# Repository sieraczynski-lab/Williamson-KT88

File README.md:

# Williamson KT88

Lampowy wzmacniacz push-pull w klasycznej topologii Williamsona (wszystkie lampy sterujące na 6SN7), z końcówką na parze KT88 w układzie ultralinearnym (UL). Projekt to wzmacniacz **onyx1944** na jego płytce VA1523:

- wersja na KT88 (zdjęcia, PCB): https://onyx1944.wordpress.com/2023/11/21/williamson-kt88/
- wersja na 6S33S (schemat i zasilacz): https://onyx1944.wordpress.com/2020/03/16/6s33s-williamson-amplifier/

Płytka **VA1523-V1.0** jest kupiona od Onyxa (bez lamp i transformatorów), a Onyx udostępnił schematy. Schemat w tym repozytorium jest przerysowany z jego schematu i **poprawiony według wartości faktycznie wlutowanych na płytce**. Pomarańczowe elementy to te, które trzeba sprawdzić albo dobrać pod toroid TTG-KT88PP i własny transformator sieciowy. Oryginalnych plików Onyxa tu nie ma, to jego praca.

> **Status: płytka w ręku, przed uruchomieniem.** Punkty pracy są szacunkowe (model lampy, Ua ≈ 465 V), do potwierdzenia pomiarem.

> ⚠️ **Wysokie napięcie.** Ua ok. 465 V, a na zimno i przy wysokim napięciu sieci więcej. Kondensatory filtrów rozładowują się przez rezystory 560 k i dzielnik żarzenia; to trwa od kilkudziesięciu sekund do kilku minut. Przed dotknięciem płytki zawsze zmierz napięcie.

## Schematy

| Plik | Zawartość |
|---|---|
| [`schematy/kanal.svg`](schematy/kanal.svg) | Jeden kanał wg VA1523: 6SN7 (wejście + katodyna) → 6SN7 (driver) → 2× KT88 UL, bias osobno dla każdej lampy |
| [`schematy/zasilacz.svg`](schematy/zasilacz.svg) | Zasilacz z płytki (osobno w każdym kanale): mostek, CLC z dławikiem 10 H, Uaa przez R128, bias, podniesienie żarzenia |
| [`schematy/plytka_zasilacza.svg`](schematy/plytka_zasilacza.svg) | Własna płytka zasilacza: bezpieczniki, miękki start K1/K2, opóźnione anody K3/K4 z R_IN, napięcia przemienne do płytki Onyxa, pomiar Ua i dioda HV |
| [`pcb/`](pcb/) | Płytki do zamówienia (KiCad 4 dla EasyEDA Standard, 5 dla EasyEDA Pro i KiCad 8, z klasami sieci): nowy zasilacz 100 × 100 mm, nowa płytka UL/trioda na oba kanały (4 przekaźniki, 100 × 66 mm) oraz z Soloista sterowanie ESP32, przełącznik kolumn, selektor. Połączenia: [`pcb/CZYTAJ_MNIE.txt`](pcb/CZYTAJ_MNIE.txt) |
| [`docs/soloist/`](docs/soloist/) | Opis sterowania i selektora (kopia z Soloista) |
| [`schematy/ul_trioda.svg`](schematy/ul_trioda.svg) | Okablowanie przełącznika UL / trioda: toroid, płytka UL, J101 Onyxa |
| [`schematy/williamson-kt88.html`](schematy/williamson-kt88.html) | Oba schematy z punktami pracy, różnicami płytka/schemat, listą zmian i uruchomieniem (otwórz w przeglądarce) |

## Najważniejsze dane

| | Wartość |
|---|---|
| Lampy | V1, V2: 6SN7 (6N8S); V5, V6: KT88 (lewy kanał; prawy V3, V4, V7, V8) |
| Front end | wejście ok. 4,3 mA / 95 V, katodyna 22k/22k ok. 4,5 mA, driver ok. 5 mA na triodę (bez balansu AC) |
| Końcówka | KT88 UL, Ua ≈ 465 V, 50–55 mA (0,50–0,55 V na 10 Ω), Ug1 ≈ −45…−55 V |
| Transformator wyjściowy | toroidy.pl **TTG-KT88PP** (u Onyxa Hammond 1650HA 6,6 kΩ) |
| Sprzężenie zwrotne | R129 15k z **odczepu 8 Ω** (ok. 12 dB), C123 niemontowany |
| Czułość / moc | ok. 0,65 V / ok. 40 W na kanał, kolumny na odczepie 4 Ω |
| Transformator sieciowy | 400 VA: 360 V (odczepy 345/375 V)/0,65 A, 58 V/100 mA, 6,3 V/8 A, 6,3 V/3 A, ekran ([docs/08](docs/08-zamowienie-toroidy.md)) |
| Dławiki | 2× 10 H / 250 mA / 45 Ω na L106 / L206 |

## Płytka a schemat Onyxa

| Element | Na schemacie | Na płytce |
|---|---|---|
| R117 / R217 | 220k / 1k | **100k / 100k** |
| R124 / R224 | 10 Ω / 470k | **10 Ω / 10 Ω** |
| C123 / C223 | 56 pF | **brak** |
| R101 | 1M | **220k** |
| R103 | 47k | **33k** |
| R104 / C102 | 47 Ω / 47 µF | **zwora / brak** |
| R111, R112 | 470k | **300k** |
| R119, R120 | 470k | **68k** |
| P101, P102 | 47k | **20k** |
| R139, R140 | 47k | **4k7** |
| R129 | 22k | **15k** |
| R134 | 10 Ω | **5,1 Ω** |
| R136 / R137 | 100k / 10k | **brak** w lewym, **300k / 68k** w prawym |
| R130–R133 | 330 Ω | **390 Ω** |
| R143–R152 | 680k | **560k** |
| R125, R126 | 100 Ω | **150 Ω** |
| R141, R142 | 10 Ω / 100 Ω | **47 Ω / 47 Ω** |

## Zasilacz, sterowanie, dodatki i obudowa

Płytka Onyxa dostaje własną, prostą płytkę zasilacza (bez prostowników i filtrów, bo te są na płytce Onyxa): miękki start, opóźnione anody, pomiar Ua. Z [Soloist-KT88](https://github.com/sieraczynski-lab/Soloist-KT88) bierze sterownik ESP32 z automatyczną korektą biasu, układ przełącznika UL / trioda (tu jedna płytka na oba kanały), przełącznik kolumn z triggerem, selektor z drabinką głośności i obudowę. Te płytki Soloista bez zmian w PCB, płytka Onyxa bez cięcia ścieżek. Szczegóły: [docs/09-integracja-soloist.md](docs/09-integracja-soloist.md), obudowa: [`obudowa/`](obudowa/).

## Decyzje i otwarte sprawy

- **Toroid TTG-KT88PP** zamiast Hammonda: sprzężenie zwrotne z odczepu 8 Ω (zbliżona głębokość pętli jak u Onyxa), kolumny na 4 Ω. Kompensację C123 dobrać na oscyloskopie, jeśli prostokąt dzwoni.
- **R128 / R228** (4k7) dobrać do własnego Ua, żeby Uaa wyszło ok. 380–420 V.
- **Driver bez balansu AC:** do V2 dawać 6SN7 o zbliżonych prądach obu triod.
- **Dodatek:** rezystor 100 Ω / 2 W między 4 Ω a COM (wzmacniacz nie pracuje bez obciążenia).
- **Odpowiedzi Onyxa (12.11.2026):** u niego TR1 to toroidy.pl TSTA-0300/001 (300 VA), radzi większy, więc 400 VA jest w porządku. Sprzężenie zwrotne z odczepu 8 Ω (zgodnie z planem). C123 i ewentualnie R102/C101 tylko pod prostokąt (u niego niepotrzebne). Pomyłki na schemacie potwierdzone. Szczegóły w [docs/07](docs/07-wersje-onyxa.md#odpowiedzi-onyxa-12112026).
- **Sprawdzone:** sieć UaFF-L2 (środek żarzenia KT88) to masa (wspólny punkt C108, C126, R142).
- Projekt równoległy: [Soloist-KT88](https://github.com/sieraczynski-lab/Soloist-KT88) (Mullard: EF86 + E88CC LTP + KT88), z podobnym transformatorem sieciowym i tymi samymi toroidami.

## Notatki

1. [Lampy KT88 Psvane: serie i różnice](docs/01-lampy-kt88.md)
2. [Transformatory wyjściowe: Hammond, toroidy.pl, Ogonowski](docs/02-transformatory-wyjsciowe.md)
3. [Topologia: Williamson, Mullard 5-20, 6S33S, 6SN7](docs/03-topologia.md)
4. [Kolumny: impedancja, zwrotnica 2,5-drożna, spadek bafla](docs/04-kolumny.md)
5. [Uruchomienie krok po kroku](docs/05-uruchomienie.md)
6. [Zamawianie płytek PCB](docs/06-pcb.md)
7. [Wersje Onyxa: zdjęcia, schemat i płytka VA1523](docs/07-wersje-onyxa.md)
8. [Specyfikacja do zamówienia w toroidy.pl](docs/08-zamowienie-toroidy.md)
9. [Zasilacz, sterowanie, dodatki i obudowa](docs/09-integracja-soloist.md)

## Generowanie schematów

Schematy są rysowane skryptem (Python 3, bez dodatkowych bibliotek):

```bash
python3 narzedzia/build.py
```

Obudowa (STEP, DXF, widoki) powstaje z `python3 narzedzia/obudowa/export.py` (wymaga `numpy` i `matplotlib`).

Skrypt [`narzedzia/gen_schemat.py`](narzedzia/gen_schemat.py) zawiera geometrię i wartości elementów. Po zmianie wartości wystarczy uruchomić `build.py` ponownie, a SVG i strona HTML w `schematy/` zostaną odświeżone.

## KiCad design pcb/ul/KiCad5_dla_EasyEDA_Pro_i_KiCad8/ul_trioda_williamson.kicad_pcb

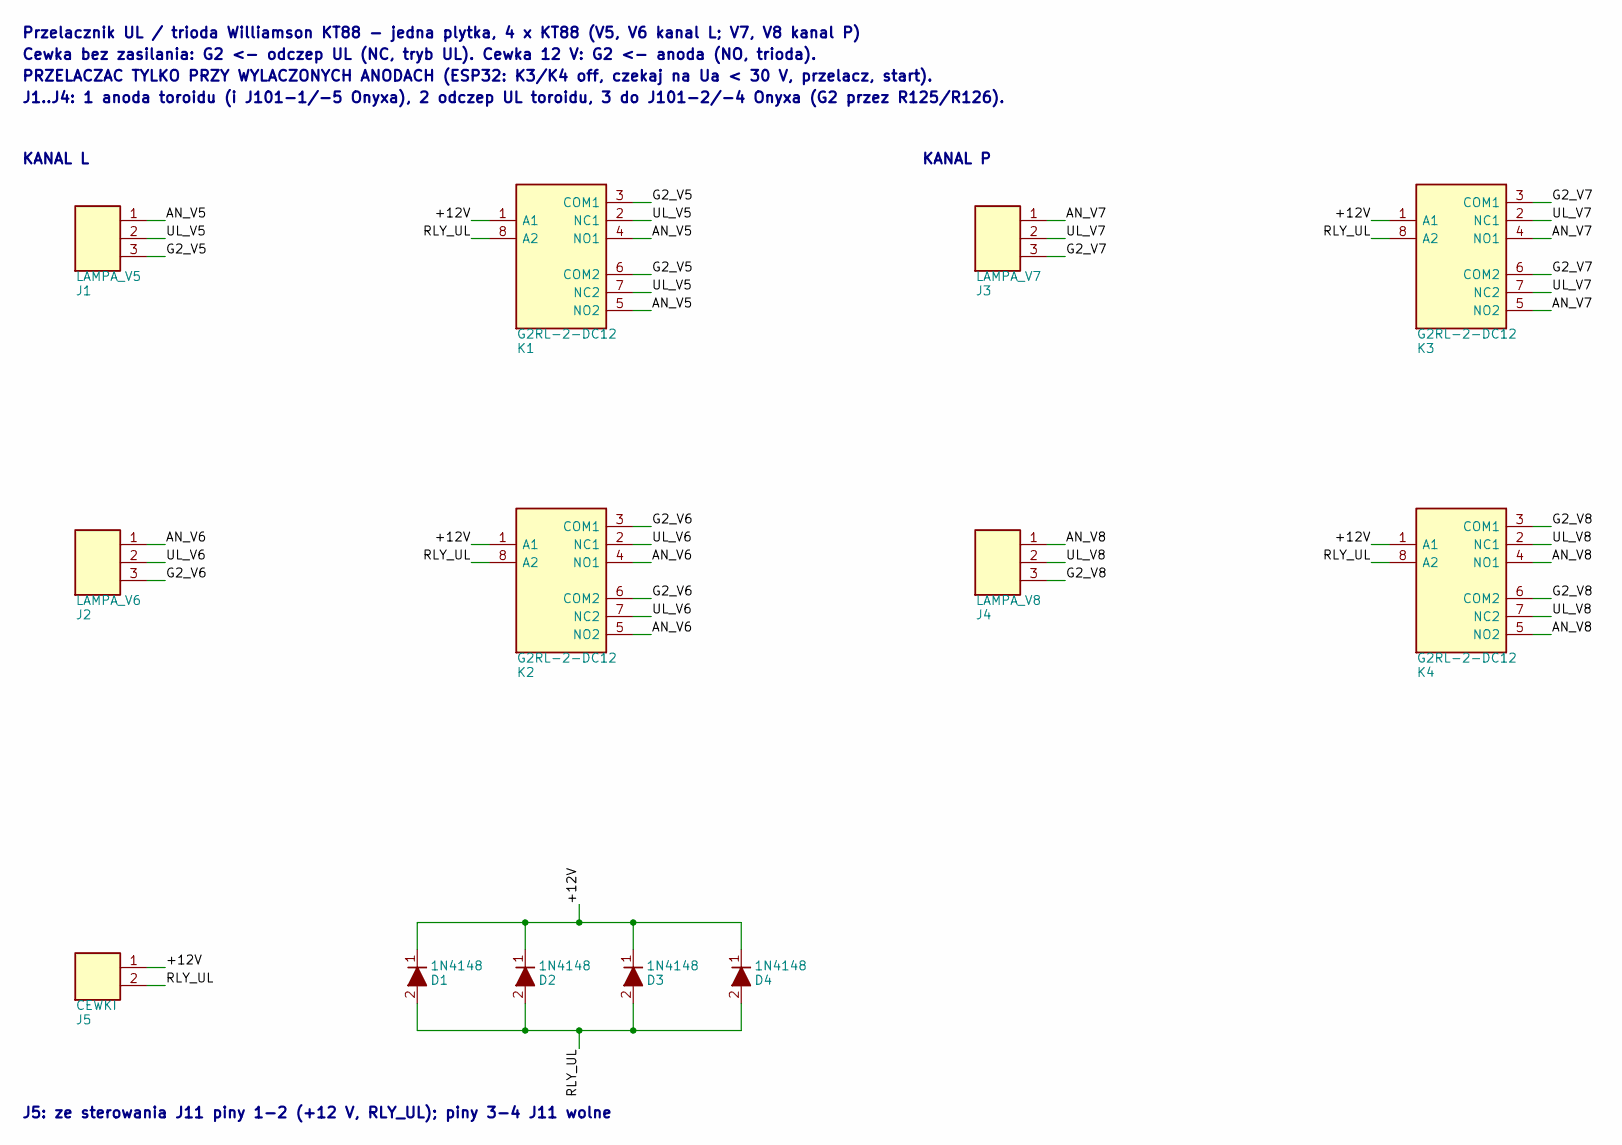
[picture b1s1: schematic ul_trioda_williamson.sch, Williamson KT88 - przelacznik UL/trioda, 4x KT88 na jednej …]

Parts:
D1, D2, D3, D4: 1N4148; D_DO-35_P7.62
J1: LAMPA_V5; TerminalBlock_1x03_P7.62_V
J2: LAMPA_V6; TerminalBlock_1x03_P7.62_V
J3: LAMPA_V7; TerminalBlock_1x03_P7.62_V
J4: LAMPA_V8; TerminalBlock_1x03_P7.62_V
J5: CEWKI; TerminalBlock_1x02_P5.08
K1, K2, K3, K4: G2RL-2-DC12; Relay_DPDT_Omron_G2RL

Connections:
+12V: D1.1 (K), D2.1 (K), D3.1 (K), D4.1 (K), J5.1, K1.1 (A1), K2.1 (A1), K3.1 (A1), K4.1 (A1)
AN_V5: J1.1, K1.4 (NO1), K1.5 (NO2)
AN_V6: J2.1, K2.4 (NO1), K2.5 (NO2)
AN_V7: J3.1, K3.4 (NO1), K3.5 (NO2)
AN_V8: J4.1, K4.4 (NO1), K4.5 (NO2)
G2_V5: J1.3, K1.3 (COM1), K1.6 (COM2)
G2_V6: J2.3, K2.3 (COM1), K2.6 (COM2)
G2_V7: J3.3, K3.3 (COM1), K3.6 (COM2)
G2_V8: J4.3, K4.3 (COM1), K4.6 (COM2)
RLY_UL: D1.2 (A), D2.2 (A), D3.2 (A), D4.2 (A), J5.2, K1.8 (A2), K2.8 (A2), K3.8 (A2), K4.8 (A2)
UL_V5: J1.2, K1.2 (NC1), K1.7 (NC2)
UL_V6: J2.2, K2.2 (NC1), K2.7 (NC2)
UL_V7: J3.2, K3.2 (NC1), K3.7 (NC2)
UL_V8: J4.2, K4.2 (NC1), K4.7 (NC2)

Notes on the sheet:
Przelacznik UL / trioda Williamson KT88 - jedna plytka, 4 x KT88 (V5, V6 kanal L; V7, V8 kanal P)
Cewka bez zasilania: G2 <- odczep UL (NC, tryb UL). Cewka 12 V: G2 <- anoda (NO, trioda).
PRZELACZAC TYLKO PRZY WYLACZONYCH ANODACH (ESP32: K3/K4 off, czekaj na Ua < 30 V, przelacz, start).
J1..J4: 1 anoda toroidu (i J101-1/-5 Onyxa), 2 odczep UL toroidu, 3 do J101-2/-4 Onyxa (G2 przez R125/R126).
KANAL L
KANAL P
J5: ze sterowania J11 piny 1-2 (+12 V, RLY_UL); piny 3-4 J11 wolne

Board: 2 copper layers, 17 parts (0 on the bottom side), 14 nets, no tracks yet.

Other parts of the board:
MH1, MH2, MH3, MH4: M3; MountingHole_M3

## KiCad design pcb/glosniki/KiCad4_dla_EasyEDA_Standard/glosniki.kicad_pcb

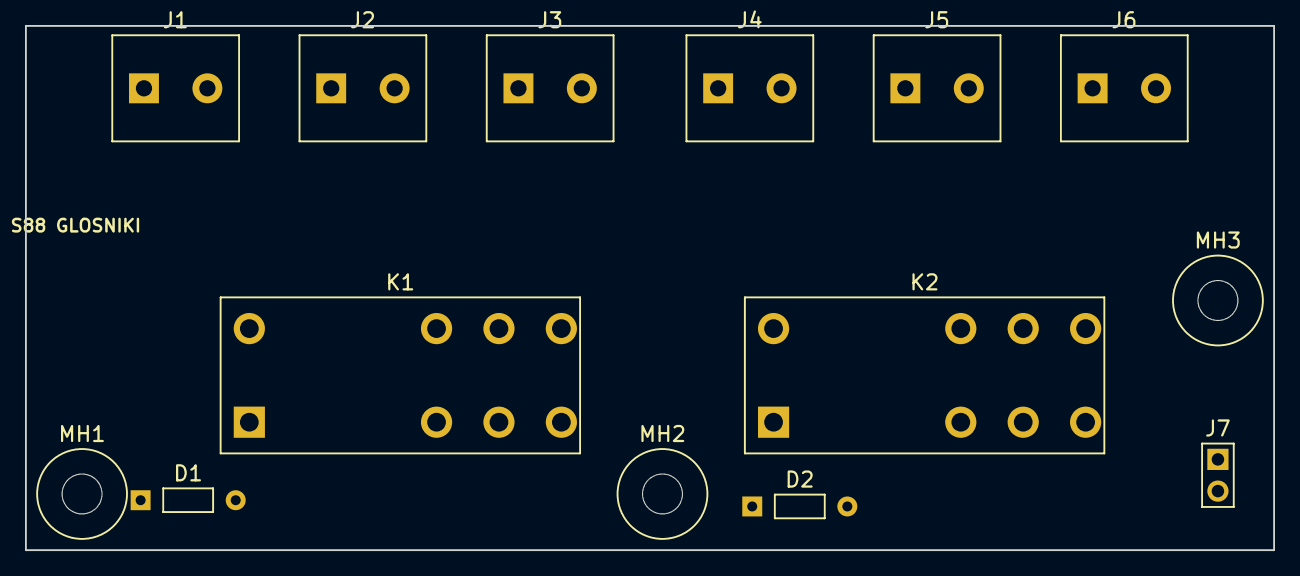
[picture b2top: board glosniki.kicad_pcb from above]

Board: 2 copper layers, 100.0 x 42.0 mm, 14 parts (0 on the bottom side), 14 nets, no tracks yet.

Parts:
D1, D2: 1N4148; D_DO-35_P7.62
J1: MARANTZ_L; TerminalBlock_1x02_P5.08
J2: LAMPA_L; TerminalBlock_1x02_P5.08
J3: KOLUMNA_L; TerminalBlock_1x02_P5.08
J4: MARANTZ_R; TerminalBlock_1x02_P5.08
J5: LAMPA_R; TerminalBlock_1x02_P5.08
J6: KOLUMNA_R; TerminalBlock_1x02_P5.08
J7: CEWKI; PinHeader_1x02_P2.54
K1, K2: G2RL-2-DC12; Relay_DPDT_Omron_G2RL
MH1, MH2, MH3: M3; MountingHole_M3

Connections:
+12V: D1.1, D2.1, J7.1, K1.1, K2.1
MAR_LN: J1.2, K1.7
MAR_LP: J1.1, K1.2
MAR_RN: J4.2, K2.7
MAR_RP: J4.1, K2.2
RLY_SPK: D1.2, D2.2, J7.2, K1.8, K2.8
SPK_LN: J3.2, K1.6
SPK_LP: J3.1, K1.3
SPK_RN: J6.2, K2.6
SPK_RP: J6.1, K2.3
TUBE_LN: J2.2, K1.5
TUBE_LP: J2.1, K1.4
TUBE_RN: J5.2, K2.5
TUBE_RP: J5.1, K2.4

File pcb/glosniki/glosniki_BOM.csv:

Oznaczenie;Wartosc;Footprint;Strona;X [mm];Y [mm];Grupa;LCSC;Uwagi
K1;G2RL-2-DC12;Relay_DPDT_Omron_G2RL;GORA;30.00;28.00;PRZEKAZNIKI GLOSNIKOW;C61458;"kanal L: bez pradu cewki kolumna <- Marantz (NC), cewka zasilona: kolumna <- Lampa (NO); + i - przelaczane"
K2;G2RL-2-DC12;Relay_DPDT_Omron_G2RL;GORA;72.00;28.00;PRZEKAZNIKI GLOSNIKOW;C61458;"kanal R: bez pradu cewki kolumna <- Marantz (NC), cewka zasilona: kolumna <- Lampa (NO); + i - przelaczane"
D1;1N4148;D_DO-35_P7.62;GORA;13.00;38.00;PRZEKAZNIKI GLOSNIKOW;;dioda cewki K1
D2;1N4148;D_DO-35_P7.62;GORA;62.00;38.50;PRZEKAZNIKI GLOSNIKOW;;dioda cewki K2
J1;MARANTZ_L;TerminalBlock_1x02_P5.08;GORA;12.00;5.00;ZLACZA;;z wyjscia glosnikowego Marantza, kanal L: 1 +, 2 -
J2;LAMPA_L;TerminalBlock_1x02_P5.08;GORA;27.00;5.00;ZLACZA;;z wtornego T101: 1 odczep 4 Ohm, 2 COM (masa Lampy)
J3;KOLUMNA_L;TerminalBlock_1x02_P5.08;GORA;42.00;5.00;ZLACZA;;do zaciskow kolumny L na tylnej sciance: 1 +, 2 -
J4;MARANTZ_R;TerminalBlock_1x02_P5.08;GORA;58.00;5.00;ZLACZA;;z Marantza, kanal R
J5;LAMPA_R;TerminalBlock_1x02_P5.08;GORA;73.00;5.00;ZLACZA;;z wtornego T201: 1 odczep 4 Ohm, 2 COM
J6;KOLUMNA_R;TerminalBlock_1x02_P5.08;GORA;88.00;5.00;ZLACZA;;do zaciskow kolumny R
J7;CEWKI;PinHeader_1x02_P2.54;GORA;95.50;36.00;ZLACZA;;z plytki sterowania J13
MH1;M3;MountingHole_M3;GORA;4.50;37.50;OTWORY;;
MH2;M3;MountingHole_M3;GORA;51.00;37.50;OTWORY;;
MH3;M3;MountingHole_M3;GORA;95.50;22.00;OTWORY;;

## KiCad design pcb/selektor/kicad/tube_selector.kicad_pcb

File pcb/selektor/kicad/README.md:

# TubeSel v0.5: selektor 4 wejść + drabinka przekaźnikowa 63 dB + sterownik I²C

Projekt KiCad 8 (otwiera się też w KiCad 9 i nowszych).

## Zawartość
- `tube_selector.kicad_pro`: projekt (klasy sieci Audio 0,4 mm / Coil 0,3 mm)
- `tube_selector.kicad_sch`: schemat (A3)
- `tube_selector.kicad_pcb`: płytka 96 × 74 mm, 2 warstwy, elementy rozmieszczone, strefy mas na obu warstwach, **bez ścieżek**
- `TubeSel.kicad_sym` + `sym-lib-table`: biblioteka symboli projektu
- `TubeSel.pretty` + `fp-lib-table`: footprint modułu DC-DC
- `BOM.csv`: lista elementów z numerami LCSC (separator `;`)
- `JLCPCB_BOM.csv`: BOM w formacie JLCPCB do zamówienia montażu (tylko elementy SMD)
- `LCSC_zamowienie.csv`: komplet elementów do samodzielnego montażu (2 płytki + zapas, ze złączami JST) do wgrania w narzędziu BOM na lcsc.com
- Podgląd schematu i rozmieszczenia: [`docs/img/selektor_*.png`](../../../docs/img/)
- Pełna dokumentacja: [`docs/11-selektor.md`](../../../docs/11-selektor.md)
- Pliki projektu wygenerował skrypt `src/selektor/gen.py`. **Po rozpoczęciu trasowania w KiCadzie źródłem prawdy są pliki KiCad.** Ponowne uruchomienie generatora (`src/selektor/gen.py`) nadpisze ścieżki (zobacz [`src/selektor/README.md`](../../../src/selektor/README.md)).

## Układ
- **Selektor K1–K4:** COM = wejście, NO = wspólna szyna, NC = 1 kΩ do masy.
- **Drabinka K5–K10:** bity 1/2/4/8/16/32 dB, impedancja ok. 10 kΩ (9,6–10,8 kΩ), rezystory cienkowarstwowe 0,1% w wartościach dostępnych w JLCPCB/LCSC. Cewka ON = stopień tłumi. Błąd tłumienia ≤ 0,21 dB dla wszystkich 64 kodów (symulacja); kanały L i R mają identyczne wartości.

| Bit | Rs | Rp |
|---|---|---|
| −1 dB | 1,10k | 80,6k |
| −2 dB | 2,00k | 32,4k |
| −4 dB | 3,75k | 17,4k |
| −8 dB | 6,20k | 6,81k |
| −16 dB | 9,10k | 2,00k |
| −32 dB | 10,0k | 270R |
- **R33/R34 10 kΩ:** terminator, wymagany do poprawnych tłumień.
- **K11 mute (fail-safe):** bez prądu cewki wyjście jest zwarte do masy. Dźwięk dopiero po załączeniu K11.
- **Sterownik:** U1 MCP23017 (I²C) → U2, U3 ULN2803 (UTC ULN2803G-S18-R, LCSC C33924; dowolny ULN2803 w SOIC-18 300 mil pasuje) → cewki. Diody gaszące są w ULN2803 (COM → +12 V).

| Wyjście MCP23017 | Przekaźnik | Funkcja |
|---|---|---|
| GPA0–GPA3 | K1–K4 | wejście 1–4 |
| GPA4–GPA7 | K5–K8 | −1, −2, −4, −8 dB |
| GPB0–GPB1 | K9–K10 | −16, −32 dB |
| GPB2 | K11 | mute (H = dźwięk) |
| GPB3–GPB7 | — | wolne |

Wyjście w stanie H = cewka załączona.

- **Zasilanie:** płytka potrzebuje tylko +12 V. 3,3 V dla MCP23017 i pull-upów I²C daje moduł DC-DC U4 (wersja 3,3 V; pinout 1 −IN, 2 +IN, 3 OUT+, 4 OUT−; rozstaw 14,17 × 8,24 mm). Pobór z 3,3 V to kilka mA.
- **J6 (JST XH 6p) do ESP32:** 1 +12 V, 2 DGND, 3 n/c, 4 SDA, 5 SCL, 6 DGND. Pin 3 celowo nie jest podłączony: nie łącz 3,3 V z ESP32 z 3,3 V tej płytki (dwa źródła napięcia).
- **Adres I²C:** SJ1–SJ3 otwarte = **0x20**. Zwarcie SJn ustawia bit An (0x20–0x27). Jeśli na tej samej magistrali jest drugi MCP23017 (np. od przekaźników biasu), ustaw tu inny adres.
- **Pull-upy I²C 4,7 kΩ (R36, R37)** są na płytce. Jeśli ESP32 też ma swoje, nic się nie stanie.

## Masy
- **GND (audio)** i **DGND (cyfrowa)** to osobne sieci i osobne strefy miedzi. DGND zajmuje dolny pas płytki pod układami scalonymi.
- **R41 (0 Ω, domyślnie nie montować)** łączy je w jednym punkcie. Zostaw puste, jeśli masa ESP32 łączy się z masą wzmacniacza w gwieździe gdzie indziej (tak jest najlepiej). Zmontuj tylko wtedy, gdy DGND nie ma innego połączenia z masą wzmacniacza.
- **R35 (0 Ω, DNP)** łączy masę audio z obudową przez MH1.

## Do sprawdzenia przed zamówieniem
1. **Biegunowość cewki G6K-2F-Y: potwierdzona.** Pin 1 = +12 V, pin 8 = do ULN2803. Przy lutowaniu ustaw znacznik pinu 1 na obudowie przekaźnika zgodnie ze znacznikiem na sitodruku; odwrotnie wlutowany polaryzowany przekaźnik nie zadziała.
2. Kolejność pinów kabli audio na J1–J5 (sitodruk „R G L”).
3. **Footprint modułu DC-DC** odwzorowałem ze zrzutu ekranu: otwory 1,0 mm, pady 2,2 mm, obrys 17,6 × 12,2 mm. Zmierz suwmiarką swój moduł (średnicę pinów i obrys) albo podmień footprint na własny.
4. Moduł DC-DC przy obciążeniu kilku mA zwykle pracuje w trybie impulsowym (burst). Jeśli w głośnikach pojawi się cichy szum lub „ćwierkanie”, pomoże dławik/ferryt w linii +3V3 albo zastąpienie modułu stabilizatorem 78L33.

## Kroki w KiCadzie
1. Otwórz `tube_selector.kicad_pro`.
2. Schemat: Inspect → Electrical Rules Checker.
3. PCB: Tools → Update PCB from Schematic (powinno nie wykryć zmian), poprowadź ścieżki (ręcznie lub wtyczką Freerouting), naciśnij **B** (wypełnienie stref) i uruchom DRC.

## Wskazówki do trasowania
- Tor audio na warstwie TOP, krótko; BOTTOM w części audio w miarę możliwości jako ciągła masa.
- Linie cewek (ULN → przekaźniki) i +12 V prowadź z dala od wejść, najlepiej prostopadle do ścieżek audio.
- Żadna ścieżka cyfrowa (SDA, SCL, DRV) nie powinna wchodzić w część audio.
- Kanały L (pady po prawej stronie przekaźników) i R (po lewej) rozdzielaj masą.

## Sterowanie
Zmiana głośności: najpierw ZAŁĄCZ nowe bity, odczekaj ~5 ms, potem WYŁĄCZ zbędne. Przejście zawsze idzie przez stan cichszy.
Po starcie MCP23017 ma wszystkie piny jako wejścia, więc wszystkie przekaźniki są wyłączone: wejście 1 niewybrane, tłumienie 0 dB i **mute aktywny**. Odblokowanie dźwięku następuje dopiero, gdy firmware ustawi wejście, głośność i GPB2 = 1.

## Montaż w JLCPCB
- `JLCPCB_BOM.csv` zawiera wszystkie elementy SMD z numerami LCSC (stan magazynu sprawdzony 22.10.2026). Plik pozycji (CPL) wygeneruj w KiCadzie po poprowadzeniu ścieżek: File → Fabrication Outputs → Component Placement (.pos), format CSV, jednostki mm.
- Złącza JST (J1–J6) i moduł DC-DC (U4) są przewlekane, więc najprościej przylutować je samemu.
- R35 i R41 (0 Ω, opcjonalne) są poza BOM-em JLCPCB.
- **Przed zatwierdzeniem zamówienia sprawdź w podglądzie JLCPCB orientację każdego przekaźnika i układu scalonego** (znacznik pinu 1). Obrócony G6K nie zadziała.

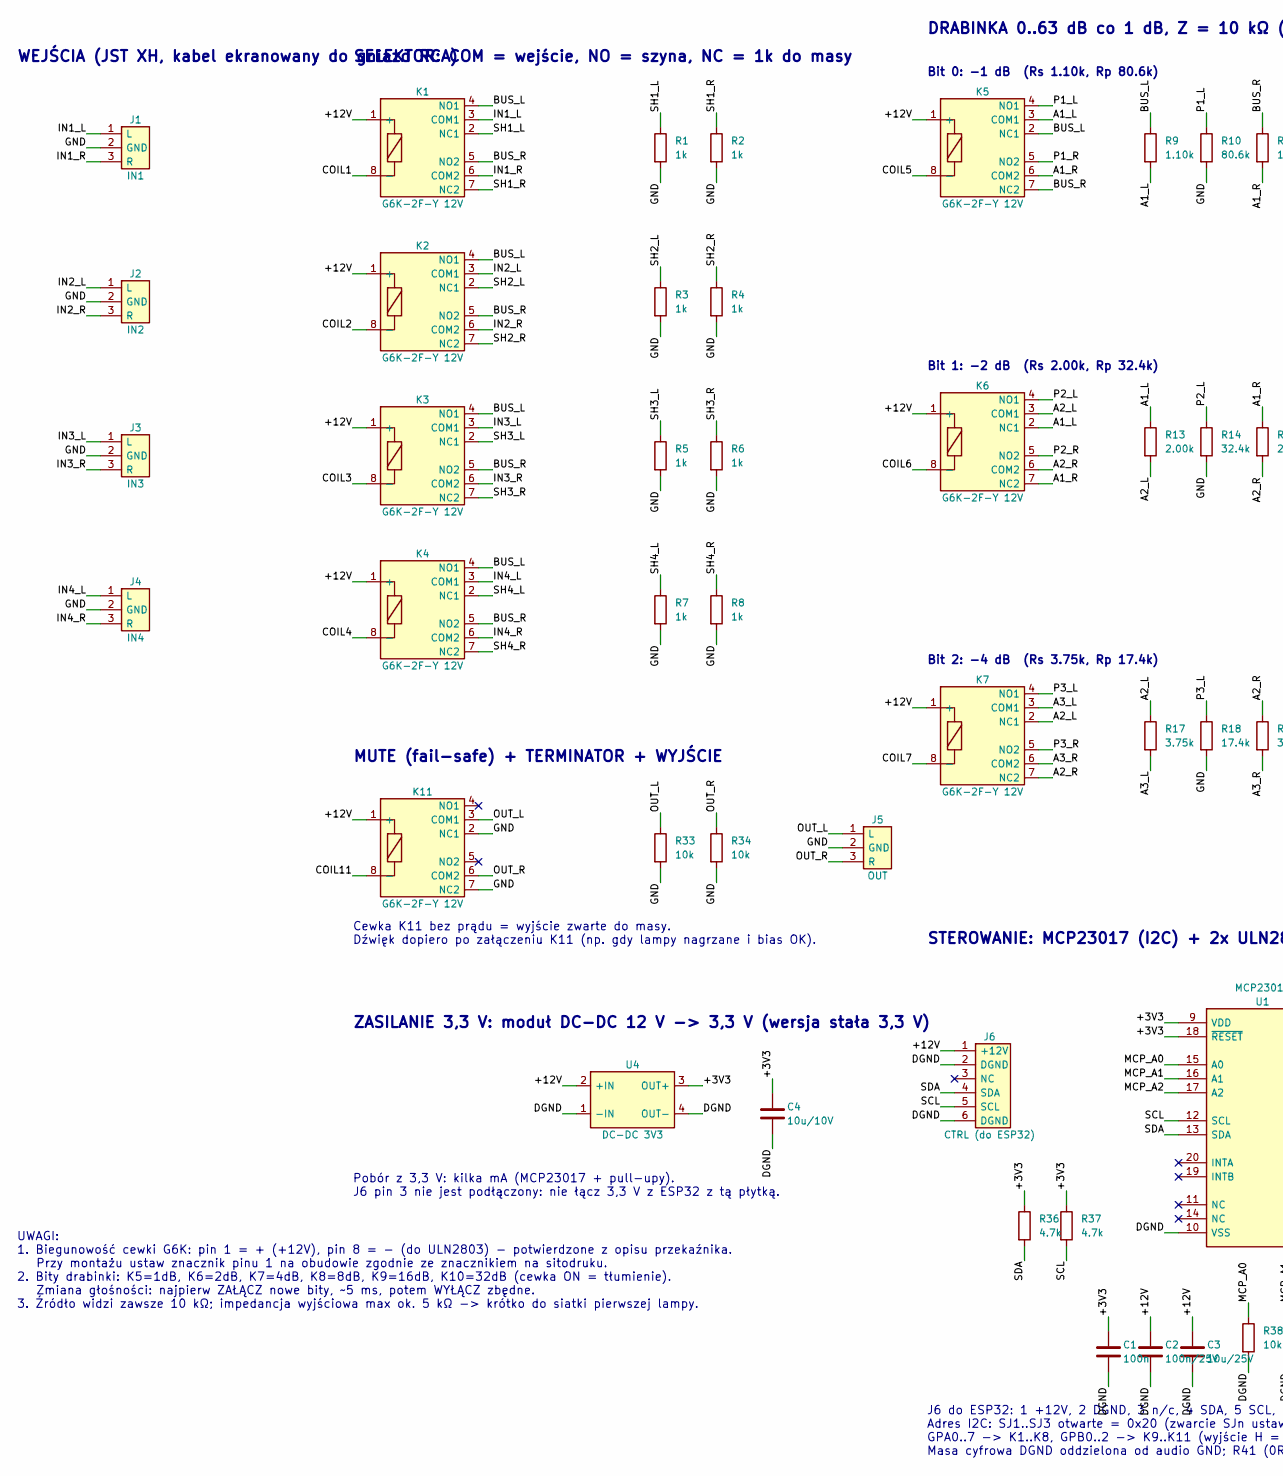
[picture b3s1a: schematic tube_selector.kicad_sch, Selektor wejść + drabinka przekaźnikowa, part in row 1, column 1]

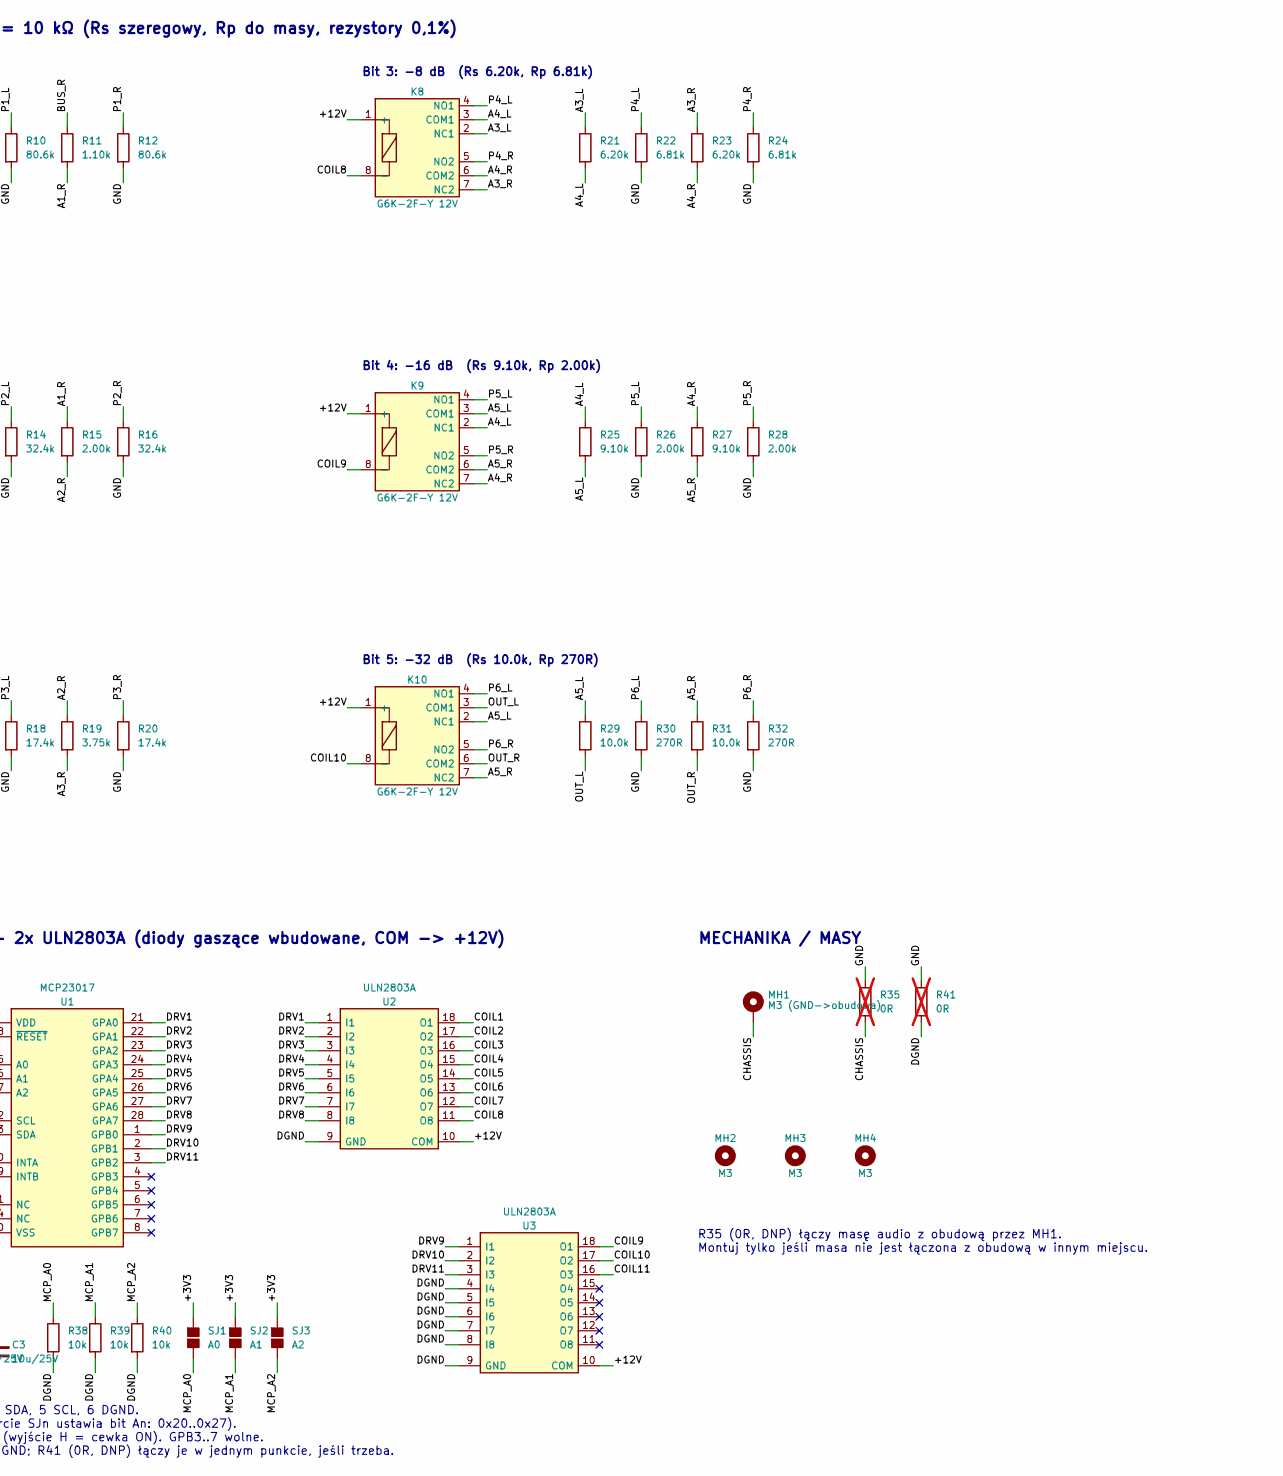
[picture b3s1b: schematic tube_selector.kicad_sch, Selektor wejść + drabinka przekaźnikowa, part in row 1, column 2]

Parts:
C1: 100n; C_0805_2012Metric; MPN CC0805KRX7R9BB104; LCSC C49678
C2: 100n/25V; C_0805_2012Metric; MPN CC0805KRX7R9BB104; LCSC C49678
C3: 10u/25V; C_1206_3216Metric; MPN CL31A106KBHNNNE; LCSC C13585
C4: 10u/10V; C_1206_3216Metric; MPN CL31A106KBHNNNE; LCSC C13585
J1: IN1; JST_XH_B3B-XH-A_1x03_P2.50mm_Vertical
J2: IN2; JST_XH_B3B-XH-A_1x03_P2.50mm_Vertical
J3: IN3; JST_XH_B3B-XH-A_1x03_P2.50mm_Vertical
J4: IN4; JST_XH_B3B-XH-A_1x03_P2.50mm_Vertical
J5: OUT; JST_XH_B3B-XH-A_1x03_P2.50mm_Vertical
J6: CTRL (do ESP32); JST_XH_B6B-XH-A_1x06_P2.50mm_Vertical; MPN JST B6B-XH-A + wtyk XHP-6
K1, K2, K3, K4, K5, K6, K7, K8, K9, K10, K11: G6K-2F-Y 12V; Relay_DPDT_Omron_G6K-2F-Y; MPN G6K-2F-Y-TR DC12; LCSC C397192
MH1: M3 (GND->obudowa); MountingHole_3.2mm_M3_Pad
MH2, MH3, MH4: M3; MountingHole_3.2mm_M3
R1, R2, R3, R4, R5, R6, R7, R8: 1k; R_0805_2012Metric; Tolerancja 1%; MPN 0805W8F1001T5E; LCSC C17513
R9, R11: 1.10k; R_0805_2012Metric; Tolerancja 0.1%; MPN ERA6AEB112V; LCSC C473284
R10, R12: 80.6k; R_0805_2012Metric; Tolerancja 0.1%; MPN RT0805BRD0780K6L; LCSC C728657
R13, R15, R26, R28: 2.00k; R_0805_2012Metric; Tolerancja 0.1%; MPN PTFR0805B2K00P9; LCSC C479096
R14, R16: 32.4k; R_0805_2012Metric; Tolerancja 0.1%; MPN TR0805B32K4P0550Z; LCSC C149970
R17, R19: 3.75k; R_0805_2012Metric; Tolerancja 0.1%; MPN AR05BTB3751A010; LCSC C374641
R18, R20: 17.4k; R_0805_2012Metric; Tolerancja 0.1%; MPN PTFR0805B17K4P9; LCSC C47115938
R21, R23: 6.20k; R_0805_2012Metric; Tolerancja 0.1%; MPN RT0805BRD076K2L; LCSC C326695
R22, R24: 6.81k; R_0805_2012Metric; Tolerancja 0.1%; MPN RT0805BRD076K81L; LCSC C728655
R25, R27: 9.10k; R_0805_2012Metric; Tolerancja 0.1%; MPN TC0525B9101T5G; LCSC C21571502
R29, R31: 10.0k; R_0805_2012Metric; Tolerancja 0.1%; MPN RT0805BRD0710KL; LCSC C110775
R30, R32: 270R; R_0805_2012Metric; Tolerancja 0.1%; MPN PTFR0805B270RN9; LCSC C351587
R33, R34: 10k; R_0805_2012Metric; Tolerancja 0.1%; MPN RT0805BRD0710KL; LCSC C110775
R35, R41: 0R; R_0805_2012Metric; not fitted
R36, R37: 4.7k; R_0805_2012Metric; Tolerancja 1%; MPN 0805W8F4701T5E; LCSC C17673
R38, R39, R40: 10k; R_0805_2012Metric; Tolerancja 1%; MPN 0805W8F1002T5E; LCSC C17414
SJ1: A0; SolderJumper-2_P1.3mm_Open_Pad1.0x1.5mm
SJ2: A1; SolderJumper-2_P1.3mm_Open_Pad1.0x1.5mm
SJ3: A2; SolderJumper-2_P1.3mm_Open_Pad1.0x1.5mm
U1: MCP23017; SOIC-28W_7.5x17.9mm_P1.27mm; MPN MCP23017-E/SO; LCSC C47023
U2, U3: ULN2803A; SOIC-18W_7.5x11.6mm_P1.27mm; MPN ULN2803G-S18-R (UTC); LCSC C33924
U4: DC-DC 3V3; DCDC_Mini_4pin_14.17x8.24mm; MPN Mini DC-DC step-down 3,3 V (pinout: 1 -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

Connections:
/+3V3: C1.1, C4.1, R36.1, R37.1, SJ1.1, SJ2.1, SJ3.1, U1.9 (VDD), U1.18 (~RESET), U4.3 (OUT+)
/+12V: C2.1, C3.1, J6.1 (+12V), K1.1 (+), K2.1 (+), K3.1 (+), K4.1 (+), K5.1 (+), K6.1 (+), K7.1 (+), K8.1 (+), K9.1 (+), K10.1 (+), K11.1 (+), U2.10 (COM), U3.10 (COM), U4.2 (+IN)
/A1_L: K5.3 (COM1), K6.2 (NC1), R9.2, R13.1
/A1_R: K5.6 (COM2), K6.7 (NC2), R11.2, R15.1
/A2_L: K6.3 (COM1), K7.2 (NC1), R13.2, R17.1
/A2_R: K6.6 (COM2), K7.7 (NC2), R15.2, R19.1
/A3_L: K7.3 (COM1), K8.2 (NC1), R17.2, R21.1
/A3_R: K7.6 (COM2), K8.7 (NC2), R19.2, R23.1
/A4_L: K8.3 (COM1), K9.2 (NC1), R21.2, R25.1
/A4_R: K8.6 (COM2), K9.7 (NC2), R23.2, R27.1
/A5_L: K9.3 (COM1), K10.2 (NC1), R25.2, R29.1
/A5_R: K9.6 (COM2), K10.7 (NC2), R27.2, R31.1
/BUS_L: K1.4 (NO1), K2.4 (NO1), K3.4 (NO1), K4.4 (NO1), K5.2 (NC1), R9.1
/BUS_R: K1.5 (NO2), K2.5 (NO2), K3.5 (NO2), K4.5 (NO2), K5.7 (NC2), R11.1
/CHASSIS: MH1.1, R35.2
/COIL1: K1.8 (-), U2.18 (O1)
/COIL2: K2.8 (-), U2.17 (O2)
/COIL3: K3.8 (-), U2.16 (O3)
/COIL4: K4.8 (-), U2.15 (O4)
/COIL5: K5.8 (-), U2.14 (O5)
/COIL6: K6.8 (-), U2.13 (O6)
/COIL7: K7.8 (-), U2.12 (O7)
/COIL8: K8.8 (-), U2.11 (O8)
/COIL9: K9.8 (-), U3.18 (O1)
/COIL10: K10.8 (-), U3.17 (O2)
/COIL11: K11.8 (-), U3.16 (O3)
/DGND: C1.2, C2.2, C3.2, C4.2, J6.2 (DGND), J6.6 (DGND), R38.2, R39.2, R40.2, R41.2, U1.10 (VSS), U2.9 (GND), U3.4 (I4), U3.5 (I5), U3.6 (I6), U3.7 (I7), U3.8 (I8), U3.9 (GND), U4.1 (-IN), U4.4 (OUT-)
/DRV1: U1.21 (GPA0), U2.1 (I1)
/DRV2: U1.22 (GPA1), U2.2 (I2)
/DRV3: U1.23 (GPA2), U2.3 (I3)
/DRV4: U1.24 (GPA3), U2.4 (I4)
/DRV5: U1.25 (GPA4), U2.5 (I5)
/DRV6: U1.26 (GPA5), U2.6 (I6)
/DRV7: U1.27 (GPA6), U2.7 (I7)
/DRV8: U1.28 (GPA7), U2.8 (I8)
/DRV9: U1.1 (GPB0), U3.1 (I1)
/DRV10: U1.2 (GPB1), U3.2 (I2)
/DRV11: U1.3 (GPB2), U3.3 (I3)
/GND: J1.2 (GND), J2.2 (GND), J3.2 (GND), J4.2 (GND), J5.2 (GND), K11.2 (NC1), K11.7 (NC2), R1.2, R2.2, R3.2, R4.2, R5.2, R6.2, R7.2, R8.2, R10.2, R12.2, R14.2, R16.2, R18.2, R20.2, R22.2, R24.2, R26.2, R28.2, R30.2, R32.2, R33.2, R34.2, R35.1, R41.1
/IN1_L: J1.1 (L), K1.3 (COM1)
/IN1_R: J1.3 (R), K1.6 (COM2)
/IN2_L: J2.1 (L), K2.3 (COM1)
/IN2_R: J2.3 (R), K2.6 (COM2)
/IN3_L: J3.1 (L), K3.3 (COM1)
/IN3_R: J3.3 (R), K3.6 (COM2)
/IN4_L: J4.1 (L), K4.3 (COM1)
/IN4_R: J4.3 (R), K4.6 (COM2)
/MCP_A0: R38.1, SJ1.2, U1.15 (A0)
/MCP_A1: R39.1, SJ2.2, U1.16 (A1)
/MCP_A2: R40.1, SJ3.2, U1.17 (A2)
/OUT_L: J5.1 (L), K10.3 (COM1), K11.3 (COM1), R29.2, R33.1
/OUT_R: J5.3 (R), K10.6 (COM2), K11.6 (COM2), R31.2, R34.1
/P1_L: K5.4 (NO1), R10.1
/P1_R: K5.5 (NO2), R12.1
/P2_L: K6.4 (NO1), R14.1
/P2_R: K6.5 (NO2), R16.1
/P3_L: K7.4 (NO1), R18.1
/P3_R: K7.5 (NO2), R20.1
/P4_L: K8.4 (NO1), R22.1
/P4_R: K8.5 (NO2), R24.1
/P5_L: K9.4 (NO1), R26.1
/P5_R: K9.5 (NO2), R28.1
/P6_L: K10.4 (NO1), R30.1
/P6_R: K10.5 (NO2), R32.1
/SCL: J6.5 (SCL), R37.2, U1.12 (SCL)
/SDA: J6.4 (SDA), R36.2, U1.13 (SDA)
/SH1_L: K1.2 (NC1), R1.1
/SH1_R: K1.7 (NC2), R2.1
/SH2_L: K2.2 (NC1), R3.1
/SH2_R: K2.7 (NC2), R4.1
/SH3_L: K3.2 (NC1), R5.1
/SH3_R: K3.7 (NC2), R6.1
/SH4_L: K4.2 (NC1), R7.1
/SH4_R: K4.7 (NC2), R8.1

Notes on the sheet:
WEJŚCIA (JST XH, kabel ekranowany do gniazd RCA)
SELEKTOR: COM = wejście, NO = szyna, NC = 1k do masy
DRABINKA 0..63 dB co 1 dB, Z = 10 kΩ (Rs szeregowy, Rp do masy, rezystory 0,1%)
Bit 0: -1 dB (Rs 1.10k, Rp 80.6k)
Bit 1: -2 dB (Rs 2.00k, Rp 32.4k)
Bit 2: -4 dB (Rs 3.75k, Rp 17.4k)
Bit 3: -8 dB (Rs 6.20k, Rp 6.81k)
Bit 4: -16 dB (Rs 9.10k, Rp 2.00k)
Bit 5: -32 dB (Rs 10.0k, Rp 270R)
MUTE (fail-safe) + TERMINATOR + WYJŚCIE
Cewka K11 bez prądu = wyjście zwarte do masy. Dźwięk dopiero po załączeniu K11 (np. gdy lampy nagrzane i bias OK).
ZASILANIE 3,3 V: moduł DC-DC 12 V -> 3,3 V (wersja stała 3,3 V)
Pobór z 3,3 V: kilka mA (MCP23017 + pull-upy). J6 pin 3 nie jest podłączony: nie łącz 3,3 V z ESP32 z tą płytką.
STEROWANIE: MCP23017 (I2C) + 2x ULN2803A (diody gaszące wbudowane, COM -> +12V)
J6 do ESP32: 1 +12V, 2 DGND, 3 n/c, 4 SDA, 5 SCL, 6 DGND. Adres I2C: SJ1..SJ3 otwarte = 0x20 (zwarcie SJn ustawia bit An: 0x20..0x27). GPA0..7 -> K1..K8, GPB0..2 -> K9..K11 (wyjście H = cewka ON). GPB3..7 wolne. Masa cyfrowa DGND oddzielona od audio GND; R41 (0R, DNP) łączy je w jednym punkcie, jeś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
MECHANIKA / MASY
R35 (0R, DNP) łączy masę audio z obudową przez MH1. Montuj tylko jeśli masa nie jest łączona z obudową w innym miejscu.
UWAGI: 1. Biegunowość cewki G6K: pin 1 = + (+12V), pin 8 = - (do ULN2803) - potwierdzone z opisu przekaźnika. Przy montażu ustaw znacznik pinu 1 na obudowie zgodnie ze znacznikiem na sitodruku. 2. Bity drabinki: K5=1dB, K6=2dB, K7=4dB, K8=8dB, K9=16dB, K10=32dB (cewka ON = tłumienie). Zmiana głośno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

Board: 2 copper layers, 73 parts (0 on the bottom side), 74 nets, no tracks yet.

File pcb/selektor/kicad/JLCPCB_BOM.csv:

Comment,Designator,Footprint,LCSC Part #
G6K-2F-Y 12V,"K1,K2,K3,K4,K5,K6,K7,K8,K9,K10,K11",Relay_DPDT_Omron_G6K-2F-Y,C397192
1k,"R1,R2,R3,R4,R5,R6,R7,R8",R_0805_2012Metric,C17513
1.10k,"R9,R11",R_0805_2012Metric,C473284
80.6k,"R10,R12",R_0805_2012Metric,C728657
2.00k,"R13,R15,R26,R28",R_0805_2012Metric,C479096
32.4k,"R14,R16",R_0805_2012Metric,C149970
3.75k,"R17,R19",R_0805_2012Metric,C374641
17.4k,"R18,R20",R_0805_2012Metric,C47115938
6.20k,"R21,R23",R_0805_2012Metric,C326695
6.81k,"R22,R24",R_0805_2012Metric,C728655
9.10k,"R25,R27",R_0805_2012Metric,C21571502
10.0k,"R29,R31",R_0805_2012Metric,C110775
270R,"R30,R32",R_0805_2012Metric,C351587
10k,"R33,R34",R_0805_2012Metric,C110775
10u/10V,C4,C_1206_3216Metric,C13585
MCP23017,U1,SOIC-28W_7.5x17.9mm_P1.27mm,C47023
ULN2803A,"U2,U3",SOIC-18W_7.5x11.6mm_P1.27mm,C33924
4.7k,"R36,R37",R_0805_2012Metric,C17673
100n,C1,C_0805_2012Metric,C49678
100n/25V,C2,C_0805_2012Metric,C49678
10u/25V,C3,C_1206_3216Metric,C13585
10k,"R38,R39,R40",R_0805_2012Metric,C17414
